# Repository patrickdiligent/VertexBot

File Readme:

# VertexBox Hardware

This is the hardware part of the little affordable robot, "VertexBot". This is a project in its ealy inception. Once the hardware is finalised, we will assemble a swarm of these lttle buggers (max 32 in a flock by design),  and test various things, and learn. The robot will have image processing and audio/DSP capabilities.

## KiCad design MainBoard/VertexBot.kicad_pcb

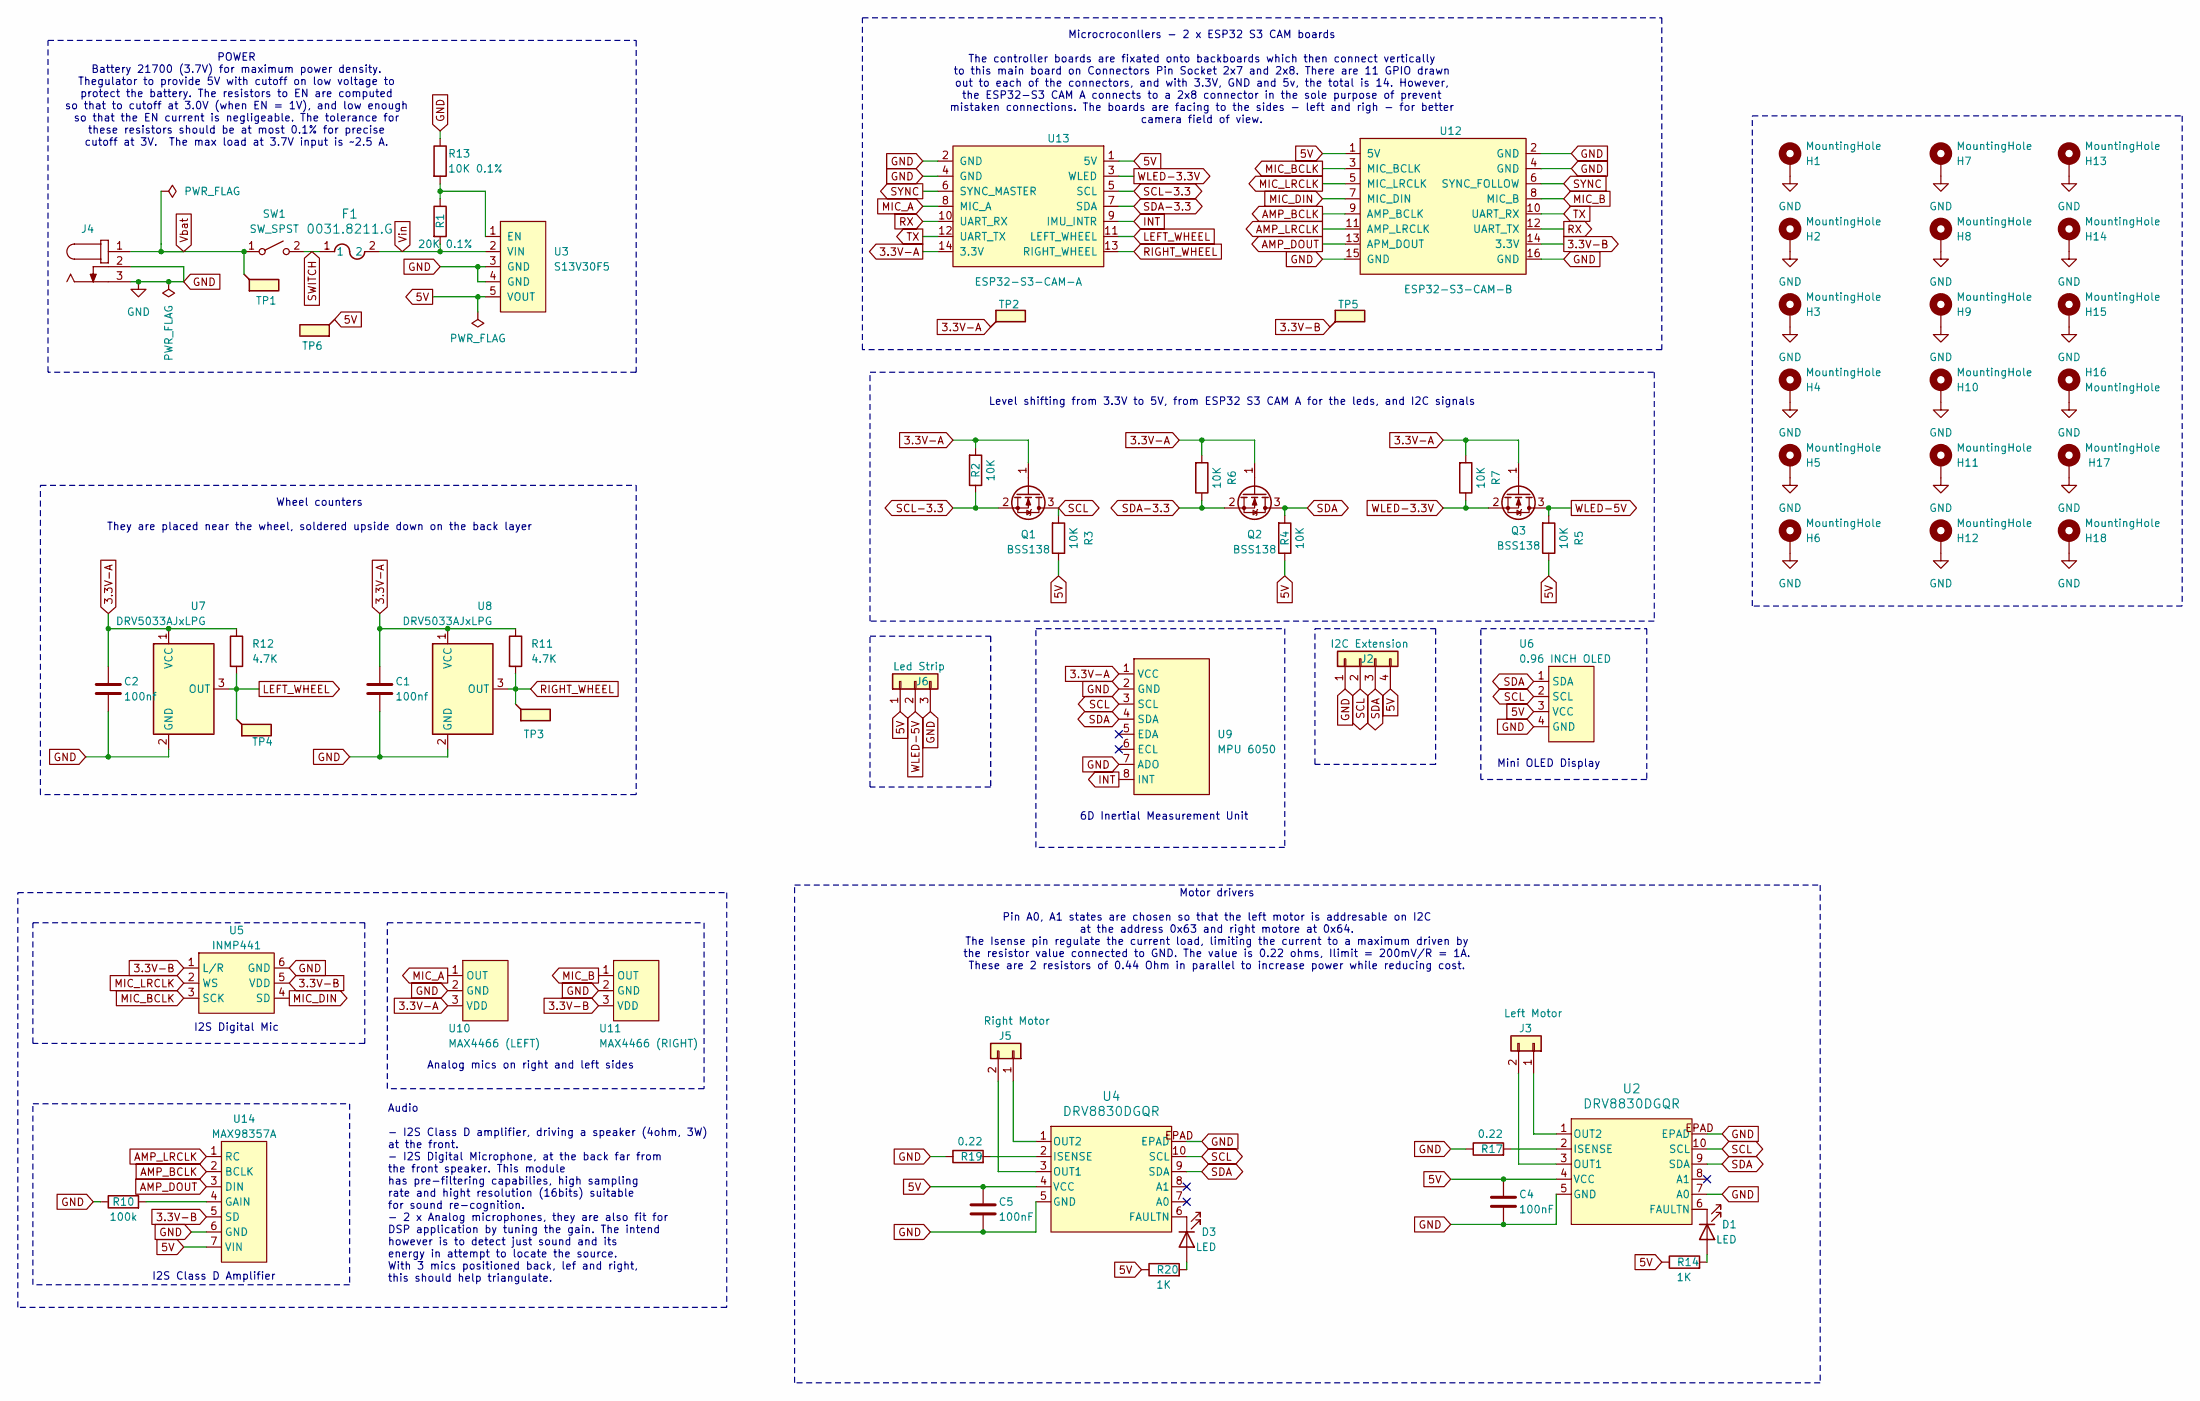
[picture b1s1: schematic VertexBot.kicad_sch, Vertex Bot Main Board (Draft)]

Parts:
C1, C2: 100nf; C_0603_1608Metric_Pad1.08x0.95mm_HandSolder; LCSC Part # C343025
C4, C5: 100nF; C_0603_1608Metric_Pad1.08x0.95mm_HandSolder; LCSC Part # C343025
D1, D3: LED; LED_0805_2012Metric_Pad1.15x1.40mm_HandSolder; LCSC Part # C264416
F1: 0031.8211.G; FUSE_0031.8211_SCH
H1, H2, H3, H4, H5, H6, H7, H8, H9, H10, H11, H12, H13, H14, H15, H16, H17, H18: MountingHole; MountingHole_3.5mm_Pad
J2: I2C Extension; PinHeader_1x04_P2.54mm_Vertical
J3: Left Motor; JST_PH_S2B-PH-K_1x02_P2.00mm_Horizontal
J4: 694106301002; J_Wurth_WR-DC_694106301002; Working Voltage (V (DC)) 30; Part Number 694106301002
J5: Right Motor; JST_PH_S2B-PH-K_1x02_P2.00mm_Horizontal
J6: Led Strip; JST_PH_B3B-PH-K_1x03_P2.00mm_Vertical
Q1, Q2, Q3: BSS138; SOT-23
R1: 20K 0.1%; R_0603_1608Metric_Pad0.98x0.95mm_HandSolder
R2, R3, R4, R5, R6, R7: 10K; R_0603_1608Metric_Pad0.98x0.95mm_HandSolder; LCSC Part # C15401
R10: 100k; R_0603_1608Metric_Pad0.98x0.95mm_HandSolder; LCSC Part # C15458
R11, R12: 4.7K; R_0603_1608Metric_Pad0.98x0.95mm_HandSolder; LCSC Part # C2784998
R13: 10K 0.1%; R_0603_1608Metric_Pad0.98x0.95mm_HandSolder; LCSC Part # C413738
R14, R20: 1K; R_0603_1608Metric_Pad0.98x0.95mm_HandSolder; LCSC Part # C2774267
R17, R19: 0.22; R_2512_6332Metric_Pad1.40x3.35mm_HandSolder; LCSC Part # C49655446
SW1: SW_SPST; L101011MS02Q
TP1, TP2, TP3, TP4, TP5, TP6: TestPoint_Flag; TestPoint_Pad_3.0x3.0mm
U2, U4: DRV8830DGQR; DGQ10_2P18X1P72; LCSC Part # C127591
U3: S13V30F5; S13V30F5_HORIZONTAL
U5: INMP441
U6: 0.96 INCH OLED; OLED_0_96_INCH
U7, U8: DRV5033AJxLPG; TO-92Flat; LCSC Part # C201608
U9: MPU 6050; MPU6050
U10: MAX4466 (LEFT); MAX4466_HORIZONTAL
U11: MAX4466 (RIGHT); MAX4466_HORIZONTAL
U12: ESP32-S3-CAM-B; CAM_B_BOARD_VERTICAL
U13: ESP32-S3-CAM-A; CAM_A_BOARD_VERTICAL
U14: MAX98357A; MAX98357

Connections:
3.3V-A: C1.1, C2.1, Q1.1 (G), Q2.1 (G), Q3.1 (G), R2.2, R6.2, R7.2, R11.1, R12.1, TP2.1, U7.1 (VCC), U8.1 (VCC), U9.1 (VCC), U10.3 (VDD), U13.14 (3.3V)
3.3V-B: TP5.1, U5.1 (L/R), U5.5 (VDD), U11.3 (VDD), U12.14 (3.3V), U14.5 (SD)
5V: C4.1, C5.1, J2.4, J6.1, R3.1, R4.1, R5.1, R14.1, R20.1, TP6.1, U2.4 (VCC), U3.5 (VOUT), U4.4 (VCC), U6.3 (VCC), U12.1 (5V), U13.1 (5V), U14.7 (VIN)
AMP_BCLK: U12.9 (AMP_BCLK), U14.2 (BCLK)
AMP_DOUT: U12.13 (APM_DOUT), U14.3 (DIN)
AMP_LRCLK: U12.11 (AMP_LRCLK), U14.1 (RC)
GND: C1.2, C2.2, C4.2, C5.2, H1.1, H2.1, H3.1, H4.1, H5.1, H6.1, H7.1, H8.1, H9.1, H10.1, H11.1, H12.1, H13.1, H14.1, H15.1, H16.1, H17.1, H18.1, J2.1, J4.2, J4.3, J6.3, R10.1, R13.1, R17.1, R19.1, U2.5 (GND), U2.7 (A0), U2.EPAD, U2.V, U3.3 (GND), U3.4 (GND), U4.5 (GND), U4.EPAD, U4.V, U5.6 (GND), U6.4 (GND), U7.2 (GND), U8.2 (GND), U9.2 (GND), U9.7 (ADO), U10.2 (GND), U11.2 (GND), U12.2 (GND), U12.4 (GND), U12.15 (GND), U12.16 (GND), U13.2 (GND), U13.4 (GND), U14.6 (GND)
INT: U9.8 (INT), U13.9 (IMU_INTR)
LEFT_WHEEL: R12.2, TP4.1, U7.3 (OUT), U13.11 (LEFT_WHEEL)
MIC_A: U10.1 (OUT), U13.8 (MIC_A)
MIC_B: U11.1 (OUT), U12.8 (MIC_B)
MIC_BCLK: U5.3 (SCK), U12.3 (MIC_BCLK)
MIC_DIN: U5.4 (SD), U12.7 (MIC_DIN)
MIC_LRCLK: U5.2 (WS), U12.5 (MIC_LRCLK)
unnamed: D1.2 (A), R14.2
unnamed: D1.1 (K), U2.6 (FAULTN)
unnamed: D3.2 (A), R20.2
unnamed: D3.1 (K), U4.6 (FAULTN)
unnamed: J3.1, U2.1 (OUT2)
unnamed: J3.2, U2.3 (OUT1)
unnamed: J5.1, U4.1 (OUT2)
unnamed: J5.2, U4.3 (OUT1)
unnamed: R17.2, U2.2 (ISENSE)
unnamed: R1.1, R13.2, U3.1 (EN)
unnamed: R19.2, U4.2 (ISENSE)
unnamed: R10.2, U14.4 (GAIN)
RIGHT_WHEEL: R11.2, TP3.1, U8.3 (OUT), U13.13 (RIGHT_WHEEL)
RX: U12.12 (UART_TX), U13.10 (UART_RX)
SCL: J2.2, Q1.3 (D), R3.2, U2.10 (SCL), U4.10 (SCL), U6.2 (SCL), U9.3 (SCL)
SCL-3.3: Q1.2 (S), R2.1, U13.5 (SCL)
SDA: J2.3, Q2.3 (D), R4.2, U2.9 (SDA), U4.9 (SDA), U6.1 (SDA), U9.4 (SDA)
SDA-3.3: Q2.2 (S), R6.1, U13.7 (SDA)
SWITCH: F1.1, SW1.2 (B)
SYNC: U12.6 (SYNC_FOLLOW), U13.6 (SYNC_MASTER)
TX: U12.10 (UART_RX), U13.12 (UART_TX)
Vbat: J4.1, SW1.1 (A), TP1.1
Vin: F1.2, R1.2, U3.2 (VIN)
WLED-3.3V: Q3.2 (S), R7.1, U13.3 (WLED)
WLED-5V: J6.2, Q3.3 (D), R5.2

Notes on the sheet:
Wheel counters They are placed near the wheel, soldered upside down on the back layer
Audio - I2S Class D amplifier, driving a speaker (4ohm, 3W) at the front. - I2S Digital Microphone, at the back far from the front speaker. This module has pre-filtering capabilies, high sampling rate and hight resolution (16bits) suitable for sound re-cognition. - 2 x Analog microphones, they are 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
Analog mics on right and left sides
POWER Battery 21700 (3.7V) for maximum power density. Thegulator to provide 5V with cutoff on low voltage to protect the battery. The resistors to EN are computed so that to cutoff at 3.0V (when EN = 1V), and low enough so that the EN current is negligeable. The tolerance for these resistors should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
Level shifting from 3.3V to 5V, from ESP32 S3 CAM A for the leds, and I2C signals
I2S Class D Amplifier
Microcroconllers - 2 x ESP32 S3 CAM boards The controller boards are fixated onto backboards which then connect vertically to this main board on Connectors Pin Socket 2x7 and 2x8. There are 11 GPIO drawn out to each of the connectors, and with 3.3V, GND and 5v, the total is 14. However, the ESP32-S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
Motor drivers Pin A0, A1 states are chosen so that the left motor is addresable on I2C at the address 0x63 and right motore at 0x64. The Isense pin regulate the current load, limiting the current to a maximum driven by the resistor value connected to GND. The value is 0.22 ohms, Ilimit = 200mV/R = 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
Mini OLED Display
I2S Digital Mic
6D Inertial Measurement Unit

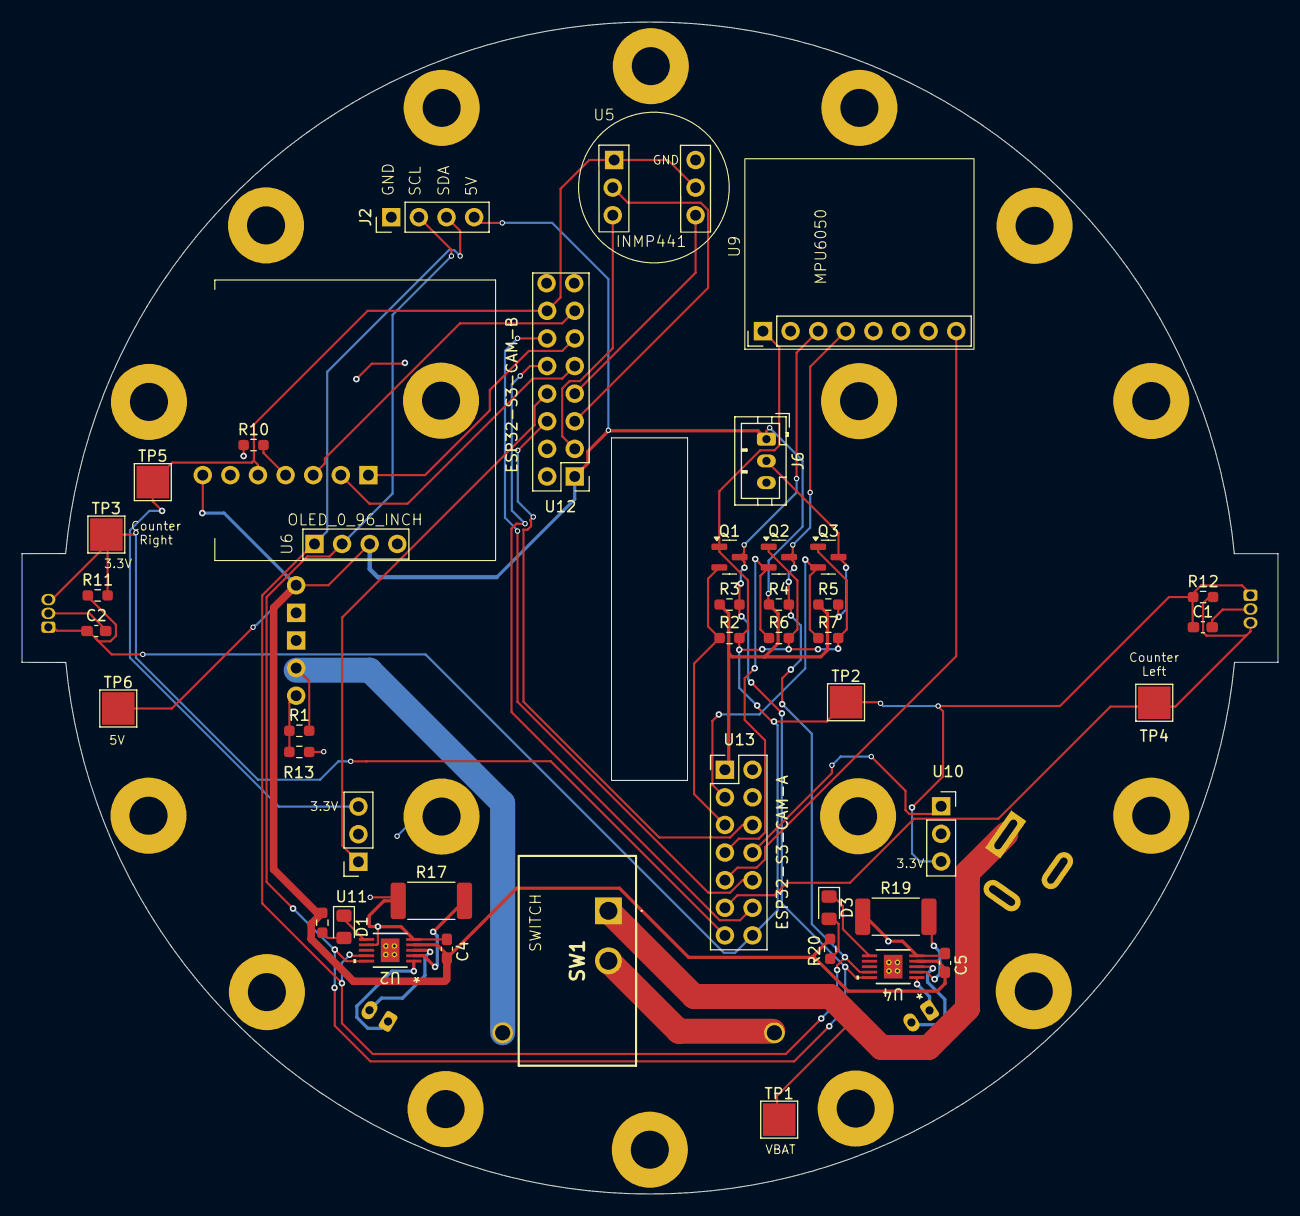
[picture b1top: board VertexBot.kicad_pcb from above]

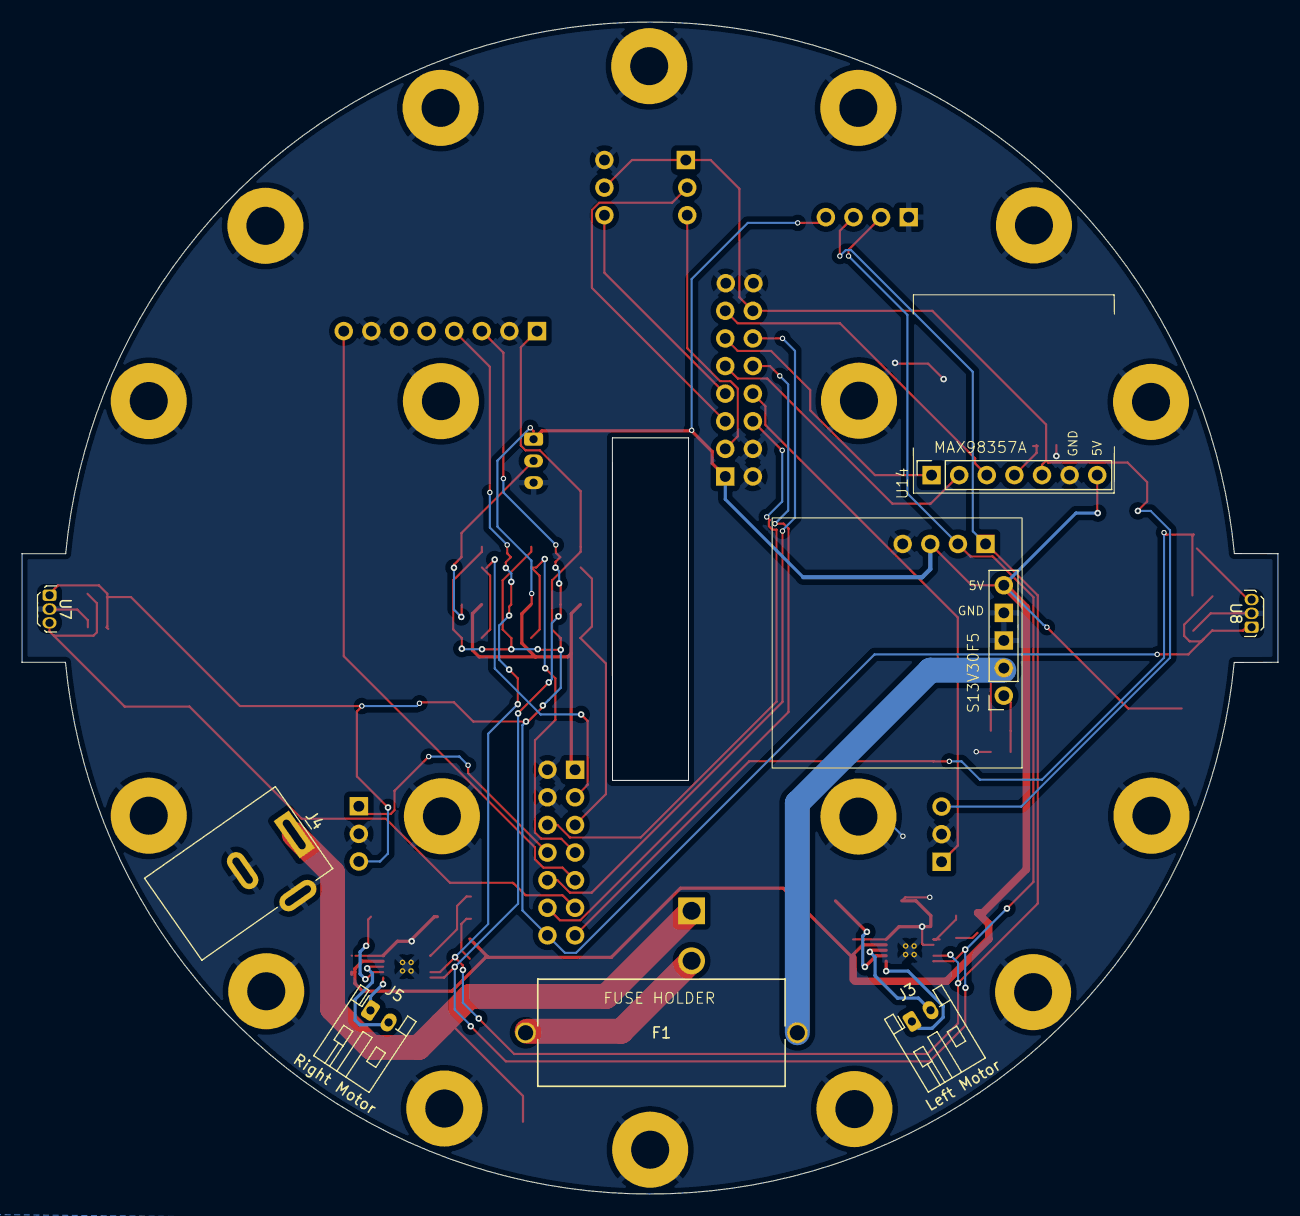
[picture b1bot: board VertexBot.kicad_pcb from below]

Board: 2 copper layers, 115.6 x 107.8 mm, 68 parts (8 on the bottom side), 39 nets.

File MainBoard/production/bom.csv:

Designator,Footprint,Quantity,Value,LCSC Part #
"C1, C2, C4, C5",0603,4,100nf,C343025
"D1, D3",0805,2,LED,C264416
"Q1, Q2, Q3",SOT-23,3,BSS138,
R1,0603,1,20K 0.1%,
R10,0603,1,100k,C15458
"R11, R12",0603,2,4.7K,C2784998 
R13,0603,1,10K 0.1%,C413738
"R14, R20",0603,2,1K,C2774267
"R17, R19",2512,2,0.22,C49655446
"R2, R3, R4, R5, R6, R7",0603,6,10K,C15401
"TP1, TP2, TP3, TP4, TP5, TP6",TestPoint_Pad_3.0x3.0mm,6,TestPoint_Flag,
"U2, U4",DGQ10_2P18X1P72,2,DRV8830DGQR,C127591
"U7, U8",TO-92Flat,2,DRV5033AJxLPG,C201608
